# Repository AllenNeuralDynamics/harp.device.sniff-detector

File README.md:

Analog Front-End for an implanted 22KOhm thermistor.

## Features:
* 1Hz highpass filter
* 1KHz lowpass filter
* Vout = 1.65 + 100\*Vin
* Common mode thermistor input filtering
* Common mode supply voltage filtering

## Wiring Diagram
TODO

## Additional Parts
These parts aren't part of the PCBA, but they are required for a complete sensing solution:

* 22kOhm thermsistor PN: GAG22K7MCD419 [digikey link](https://www.digikey.com/en/products/detail/te-connectivity-measurement-specialties/GAG22K7MCD419/5277253)
* Flexible 2-conductor 36AWG Shielded TAU cable PN: TAU-3607.02 [link](https://www.micronmeters.com/product/tau-cable-36-awg)
* 2-Pin Molex Connector Plug PN: 0533984002 ([link](https://www.digikey.com/en/products/detail/molex/0533984002/15622916))
* 2-Pin Molex Connector Socket PN: 0151340206 ([link](https://www.digikey.com/en/products/detail/molex/0151340206/6198199))

### Old Connectors
These connectors are no longer used:
* 2-pin Mill Max Connector pins PN: 850-10-002-20-001000 [digikey link](https://www.digikey.com/en/products/detail/mill-max-manufacturing-corp/800-10-002-20-001000/7762570)
* 2-socket Mill Max Connector socket PN: 801-47-002-10-012000 [digikey link](https://www.digikey.com/en/products/detail/mill-max-manufacturing-corp/801-47-002-10-012000/7364072)

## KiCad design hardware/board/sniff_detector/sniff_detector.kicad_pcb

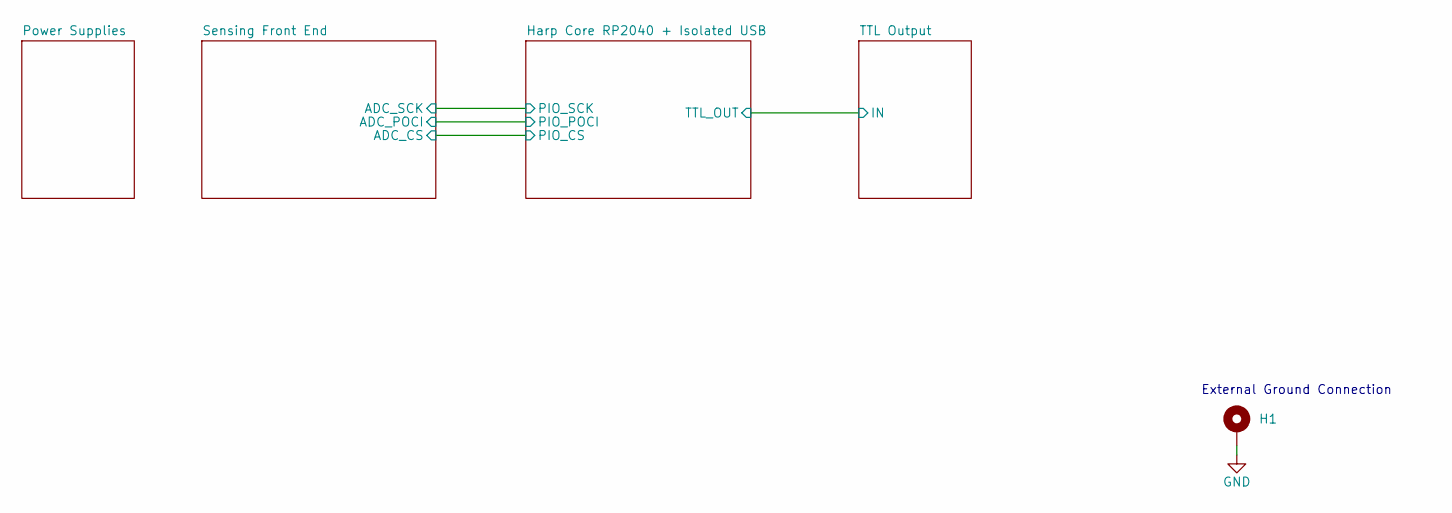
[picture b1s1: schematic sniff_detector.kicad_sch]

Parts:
H1: MountingHole_Pad; Terminal_Keystone_779x_EdgeMount_Horizontal

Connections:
GND: H1.1; also elsewhere on the board

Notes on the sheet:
External Ground Connection

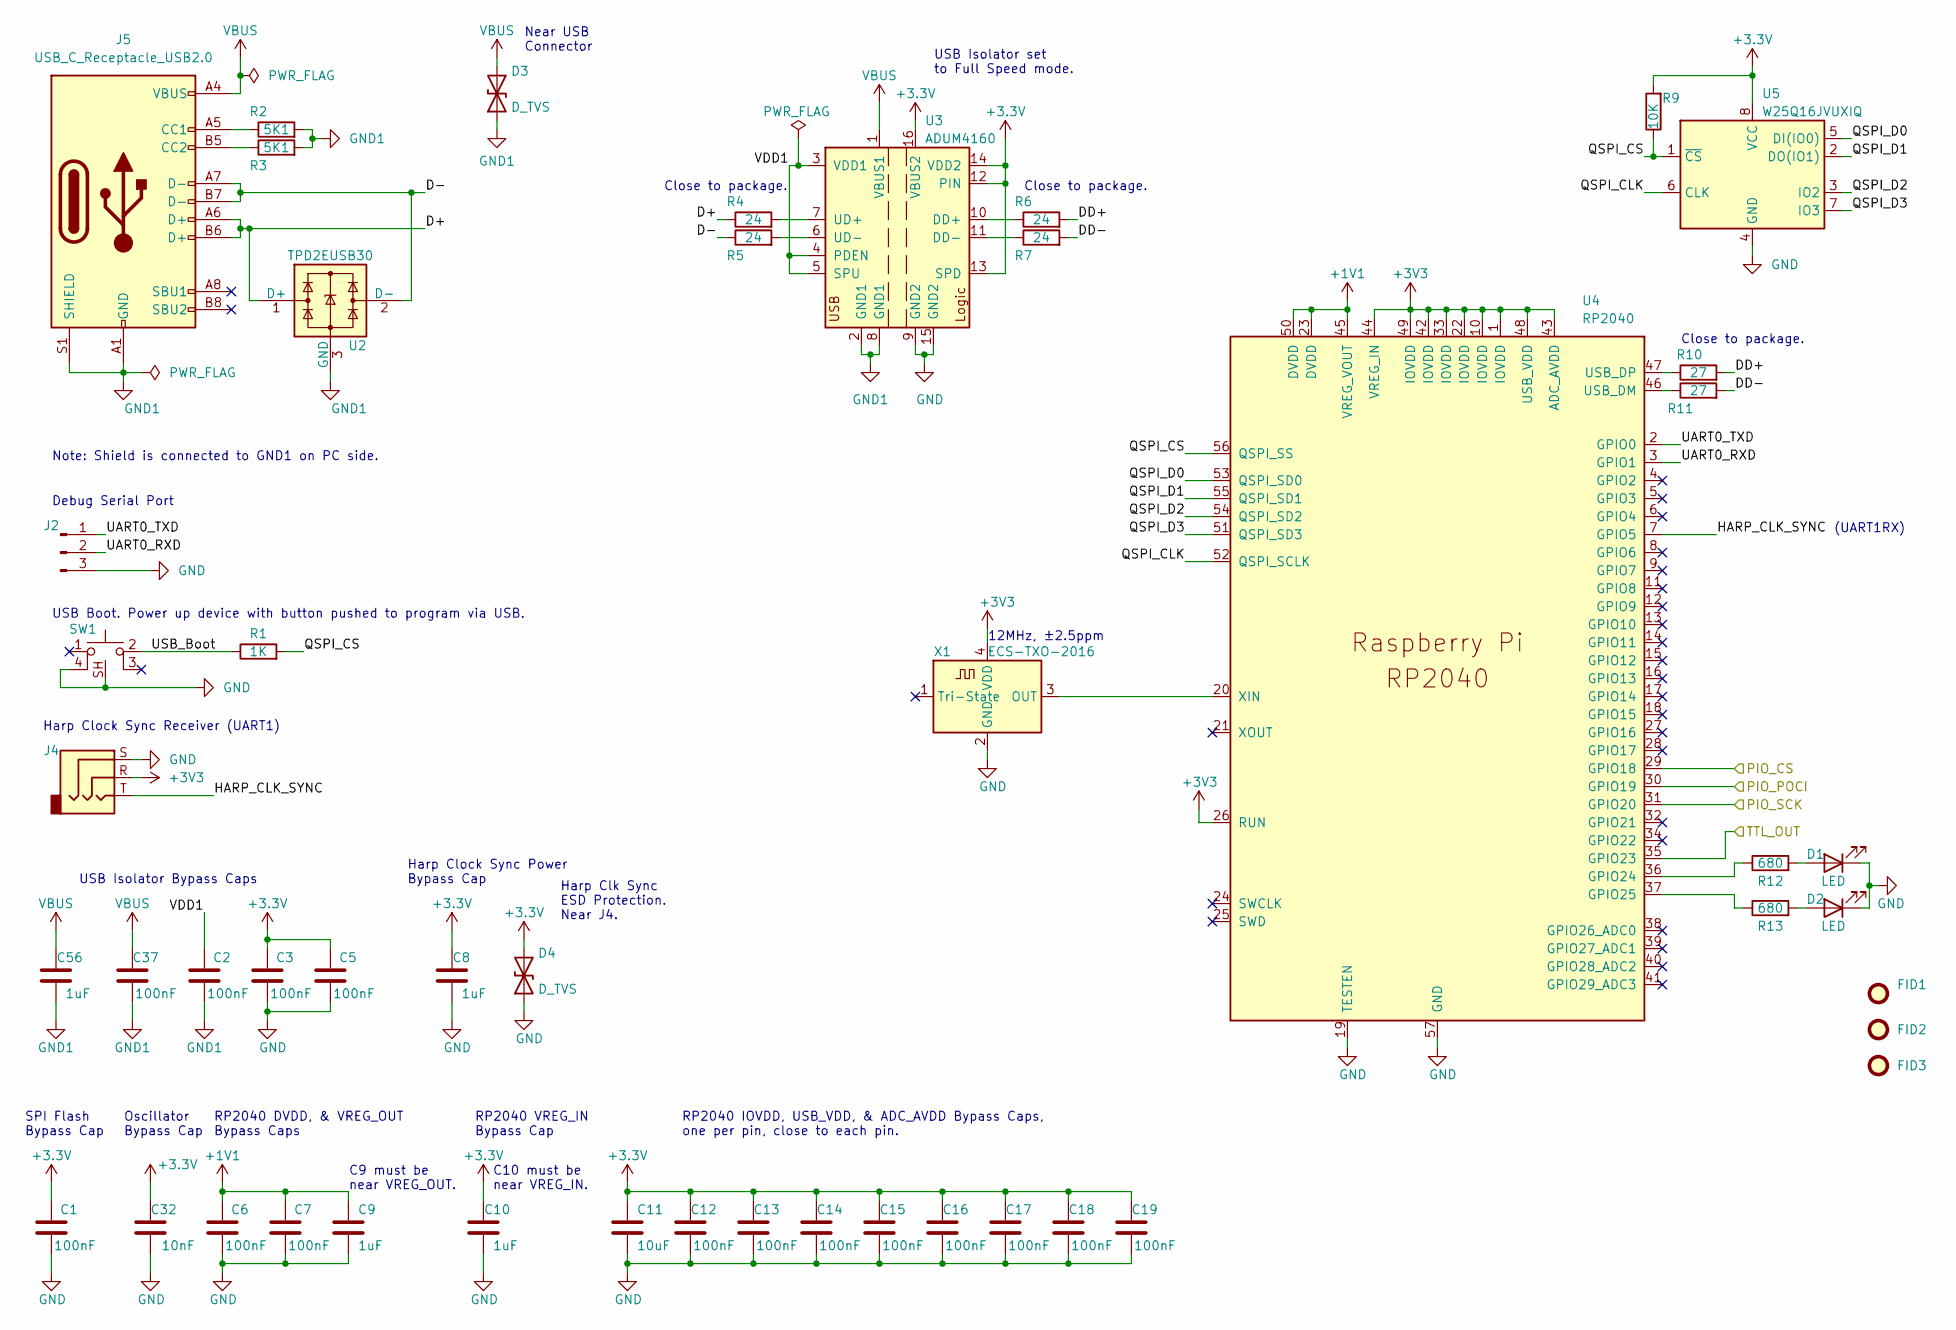
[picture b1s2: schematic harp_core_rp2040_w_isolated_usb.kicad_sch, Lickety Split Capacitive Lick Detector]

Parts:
C1, C2, C3, C5, C6, C7, C12, C13, C14, C15, C16, C17, C18, C19, C37: 100nF; C_0402_1005Metric; Rated Voltage 16V; Tolerance 10%
C8, C9, C10, C56: 1uF; C_0402_1005Metric; Rated Voltage 35V; Voltage 35V
C11: 10uF; C_0603_1608Metric; Rated Voltage 25V; Tolerance 10%
C32: 10nF; C_0402_1005Metric; Rated Voltage 25V; Tolerance 10%
D1, D2: LED; LED_0603_1608Metric_Pad1.05x0.95mm_HandSolder
D3, D4: D_TVS; D_0402_1005Metric
FID1, FID2, FID3: Fiducial; Fiducial_0.5mm_Mask1mm
J2: Conn_01x03_Male; PinHeader_1x03_P2.54mm_Vertical
J4: AudioJack3; Jack_3.5mm_CUI_SJ-3523-SMT_Horizontal
J5: USB_C_Receptacle_USB2.0; USB_C_Receptacle_JAE_DX07S016JA1R1500
R1: 1K; R_0402_1005Metric; Tolerance 1%
R2, R3: 5K1; R_0402_1005Metric; Tolerance 1%
R4, R5, R6, R7: 24; R_0402_1005Metric; Tolerance 1%
R9: 10K; R_0402_1005Metric
R10, R11: 27; R_0402_1005Metric; Tolerance 1%
R12, R13: 680; R_0402_1005Metric; Tolerance 1%
SW1: SW_Push_1P1T-SH_NO_Vertical_Wuerth_WS-TASV
U2: TPD2EUSB30; Texas_DRT-3
U3: ADUM4160; SOIC-16W_7.5x10.3mm_P1.27mm
U4: RP2040; RP2040-QFN-56
U5: W25Q16JVUXIQ; Winbond-8USON-2x3mm
X1: ECS-TXO-2016; Crystal_SMD_2016-4Pin_2.0x1.6mm; Tolerance ±2.5ppm

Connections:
+1V1: C6.2, C7.2, C9.1, U4.23 (DVDD), U4.45 (VREG_VOUT), U4.50 (DVDD)
/Harp Core RP2040 + Isolated USB/D+: J5.A6 (D+), J5.B6 (D+), R4.1, U2.1 (D+)
/Harp Core RP2040 + Isolated USB/D-: J5.A7 (D-), J5.B7 (D-), R5.1, U2.2 (D-)
/Harp Core RP2040 + Isolated USB/DD+: R6.2, R10.2
/Harp Core RP2040 + Isolated USB/DD-: R7.2, R11.2
/Harp Core RP2040 + Isolated USB/HARP_CLK_SYNC: J4.T, U4.7 (GPIO5)
/Harp Core RP2040 + Isolated USB/PIO_CS: U4.29 (GPIO18); also elsewhere on the board
/Harp Core RP2040 + Isolated USB/PIO_POCI: U4.30 (GPIO19); also elsewhere on the board
/Harp Core RP2040 + Isolated USB/PIO_SCK: U4.31 (GPIO20); also elsewhere on the board
/Harp Core RP2040 + Isolated USB/QSPI_CLK: U4.52 (QSPI_SCLK), U5.6 (CLK)
/Harp Core RP2040 + Isolated USB/QSPI_CS: R1.2, R9.1, U4.56 (QSPI_SS), U5.1 (~CS)
/Harp Core RP2040 + Isolated USB/QSPI_D0: U4.53 (QSPI_SD0), U5.5 (DI(IO0))
/Harp Core RP2040 + Isolated USB/QSPI_D1: U4.55 (QSPI_SD1), U5.2 (DO(IO1))
/Harp Core RP2040 + Isolated USB/QSPI_D2: U4.54 (QSPI_SD2), U5.3 (IO2)
/Harp Core RP2040 + Isolated USB/QSPI_D3: U4.51 (QSPI_SD3), U5.7 (IO3)
/Harp Core RP2040 + Isolated USB/TTL_OUT: U4.35 (GPIO23); also elsewhere on the board
/Harp Core RP2040 + Isolated USB/UART0_RXD: J2.2, U4.3 (GPIO1)
/Harp Core RP2040 + Isolated USB/UART0_TXD: J2.1, U4.2 (GPIO0)
/Harp Core RP2040 + Isolated USB/USB_Boot: R1.1, SW1.2
/Harp Core RP2040 + Isolated USB/VDD1: C2.2, U3.3 (VDD1), U3.4 (PDEN), U3.5 (SPU)
GND: C1.1, C3.1, C5.1, C6.1, C7.1, C8.2, C9.2, C10.2, C11.2, C12.1, C13.1, C14.1, C15.1, C16.1, C17.1, C18.1, C19.1, C32.1, D1.1 (K), D2.1 (K), D4.1 (A1), J2.3, J4.S, SW1.4, SW1.SH, U3.9 (GND2), U3.15 (GND2), U4.19 (TESTEN), U4.57 (GND), U5.4 (GND), X1.2 (GND); also elsewhere on the board
GND1: C2.1, C37.1, C56.2, D3.1 (A1), J5.A1 (GND), J5.A12 (GND), J5.B1 (GND), J5.B12 (GND), J5.S1 (SHIELD), R2.2, R3.2, U2.3 (GND), U3.2 (GND1), U3.8 (GND1)
unnamed: D1.2 (A), R12.2
unnamed: D2.2 (A), R13.2
unnamed: J5.A5 (CC1), R2.1
unnamed: J5.B5 (CC2), R3.1
unnamed: R6.1, U3.10 (DD+)
unnamed: R7.1, U3.11 (DD-)
unnamed: R4.2, U3.7 (UD+)
unnamed: R5.2, U3.6 (UD-)
unnamed: R12.1, U4.36 (GPIO24)
unnamed: R13.1, U4.37 (GPIO25)
unnamed: R11.1, U4.46 (USB_DM)
unnamed: R10.1, U4.47 (USB_DP)
unnamed: U4.20 (XIN), X1.3 (OUT)
VBUS: C37.2, C56.1, D3.2 (A2), J5.A4 (VBUS), J5.A9 (VBUS), J5.B4 (VBUS), J5.B9 (VBUS), U3.1 (VBUS1)

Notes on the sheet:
Close to package.
Near USB Connector
(UART1RX)
Harp Clk Sync ESD Protection. Near J4.
RP2040 VREG_IN Bypass Cap
Oscillator Bypass Cap
Harp Clock Sync Power Bypass Cap
C10 must be near VREG_IN.
RP2040 DVDD, & VREG_OUT Bypass Caps
Debug Serial Port
USB Boot. Power up device with button pushed to program via USB.
C9 must be near VREG_OUT.
Harp Clock Sync Receiver (UART1)
12MHz, ±2.5ppm
Note: Shield is connected to GND1 on PC side.
RP2040 IOVDD, USB_VDD, & ADC_AVDD Bypass Caps, one per pin, close to each pin.
USB Isolator Bypass Caps
SPI Flash Bypass Cap
USB Isolator set to Full Speed mode.

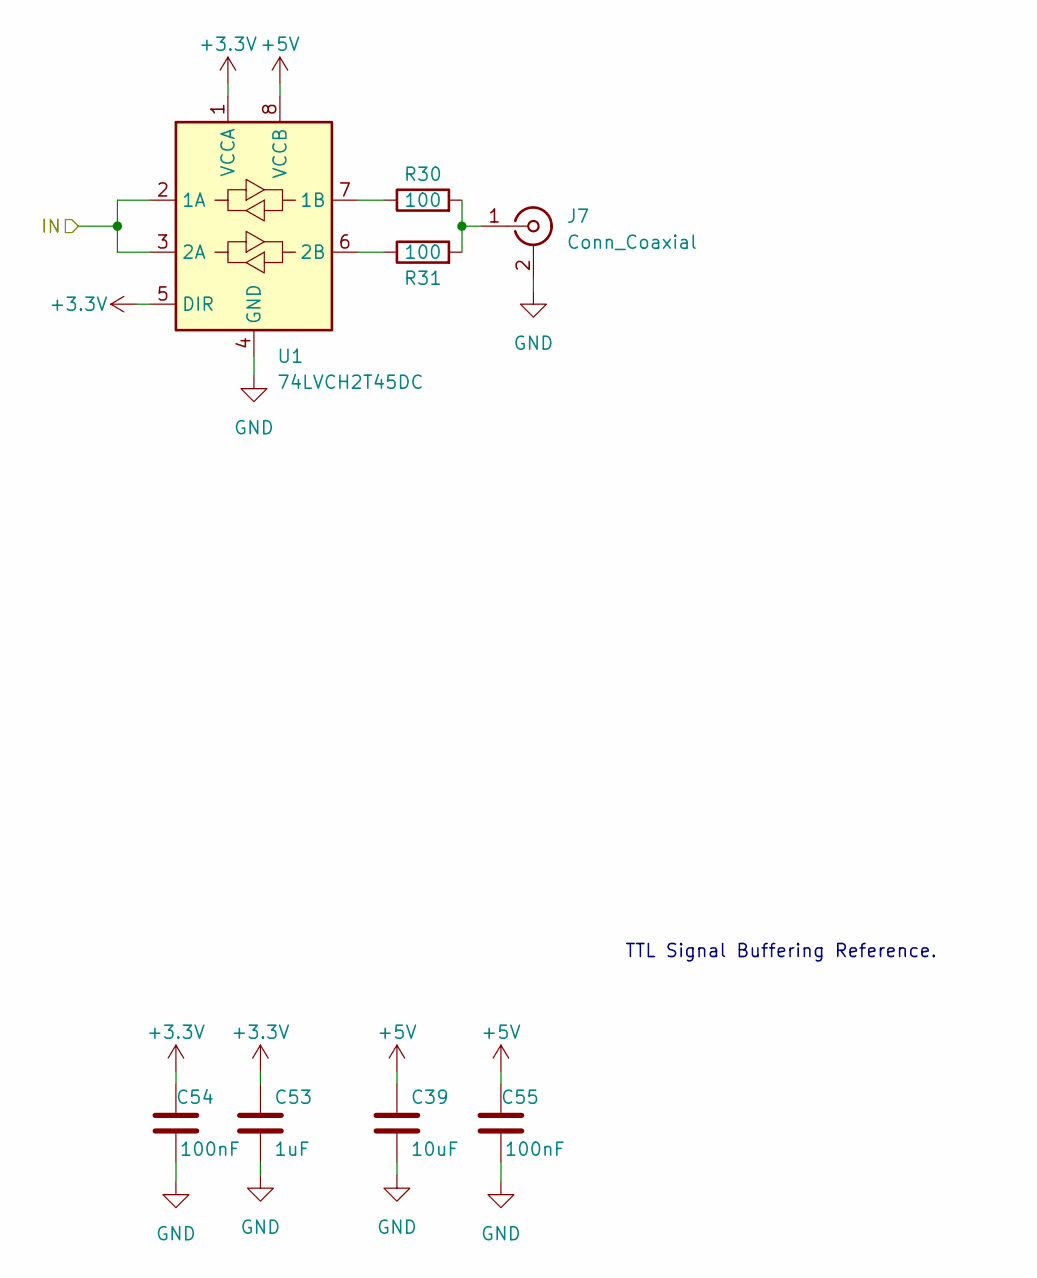
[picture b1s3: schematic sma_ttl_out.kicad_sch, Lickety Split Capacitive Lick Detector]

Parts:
C39: 10uF; C_0603_1608Metric; Rated Voltage 25V; Tolerance 10%
C53: 1uF; C_0402_1005Metric; Rated Voltage 35V; Voltage 35V
C54, C55: 100nF; C_0402_1005Metric; Rated Voltage 16V; Tolerance 10%
J7: Conn_Coaxial; SMA_TE_Connectivity_CONSMA002-SMD-G-T_Horizontal
R30, R31: 100; R_0603_1608Metric_Pad0.98x0.95mm_HandSolder; Tolerance 1%
U1: 74LVCH2T45DC; VSSOP-8_2.3x2mm_P0.5mm

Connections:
+5V: C39.1, C55.2, U1.8 (VCCB); also elsewhere on the board
/Harp Core RP2040 + Isolated USB/TTL_OUT: U1.2 (1A), U1.3 (2A); also elsewhere on the board
GND: C39.2, C53.2, C54.1, C55.1, J7.2 (Ext), U1.4 (GND); also elsewhere on the board
unnamed: J7.1 (In), R30.2, R31.2
unnamed: R30.1, U1.7 (1B)
unnamed: R31.1, U1.6 (2B)

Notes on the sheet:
TTL Signal Buffering Reference.

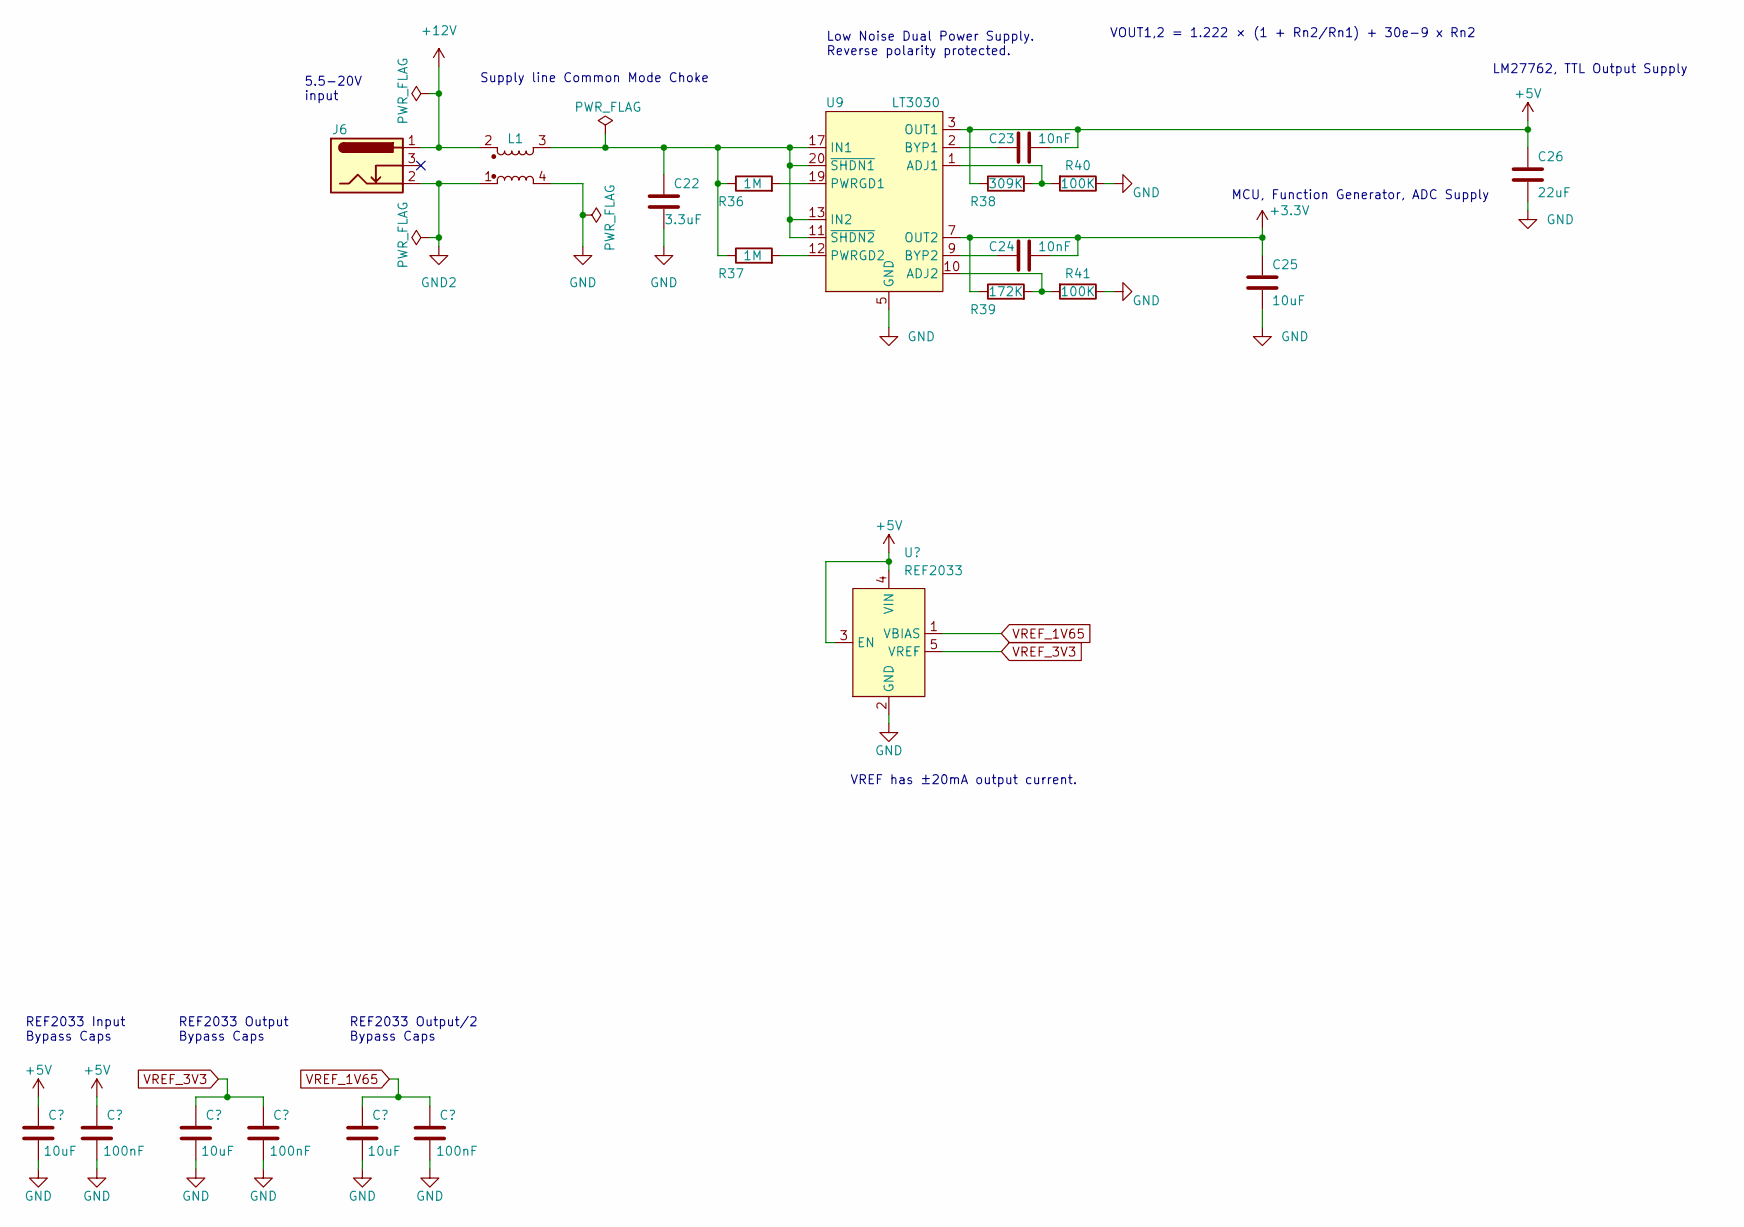
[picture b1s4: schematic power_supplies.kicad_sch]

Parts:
C22: 3.3uF; C_0805_2012Metric; Rated Voltage 25V; Tolerance 10%
C23, C24: 10nF; C_0402_1005Metric; Rated Voltage 25V; Tolerance 10%
C25: 10uF; C_0603_1608Metric; Rated Voltage 25V; Tolerance 10%
C26: 22uF; C_0805_2012Metric; Rated Voltage 25V; Voltage 25V
C35, C38, C41: 10uF; C_0603_1608Metric; Tolerance 10%; Voltage 25V
C36, C40, C42: 100nF; C_0402_1005Metric; Tolerance 10%; Voltage 16V
J6: Barrel_Jack_Switch; BarrelJack_CUI_PJ-102AH_Horizontal
L1: L_Coupled_1423; L_CommonModeChoke_TDKCorporation_1210
R36, R37: 1M; R_0402_1005Metric; Tolerance 1%
R38: 309K; R_0402_1005Metric; Tolerance 0.1%
R39: 172K; R_0402_1005Metric; Tolerance 1%
R40, R41: 100K; R_0402_1005Metric; Tolerance 0.1%
U8: REF2033; SOT-23-5
U9: LT3030; ETSSOP-20-1EP_4.4x6.5mm_P0.65mm_EP3x4.2mm

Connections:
+5V: C23.1, C26.1, C35.1, C36.2, R38.1, U8.3 (EN), U8.4 (VIN), U9.3 (OUT1), U9.4 (OUT1); also elsewhere on the board
+12V: J6.1, L1.2
GND: C22.2, C25.2, C26.2, C35.2, C36.1, C38.2, C40.1, C41.2, C42.1, L1.4, R40.1, R41.1, U8.2 (GND), U9.5 (GND), U9.6 (GND), U9.15 (GND), U9.16 (GND), U9.21 (GND); also elsewhere on the board
GND2: J6.2, L1.1
IN1: C22.1, L1.3, R36.1, R37.1, U9.11 (~SHDN2), U9.13 (IN2), U9.14 (IN2), U9.17 (IN1), U9.18 (IN1), U9.20 (~SHDN1)
unnamed: R38.2, R40.2, U9.1 (ADJ1)
unnamed: R39.2, R41.2, U9.10 (ADJ2)
unnamed: C23.2, U9.2 (BYP1)
unnamed: C24.2, U9.9 (BYP2)
unnamed: R36.2, U9.19 (PWRGD1)
unnamed: R37.2, U9.12 (PWRGD2)
VREF_1V65: C41.1, C42.2, U8.1 (VBIAS); also elsewhere on the board
VREF_3V3: C38.1, C40.2, U8.5 (VREF); also elsewhere on the board

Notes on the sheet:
REF2033 Input Bypass Caps
REF2033 Output/2 Bypass Caps
MCU, Function Generator, ADC Supply
5.5-20V input
REF2033 Output Bypass Caps
VOUT1,2 = 1.222 × (1 + Rn2/Rn1) + 30e-9 x Rn2
Supply line Common Mode Choke
VREF has ±20mA output current.
Low Noise Dual Power Supply. Reverse polarity protected.
LM27762, TTL Output Supply

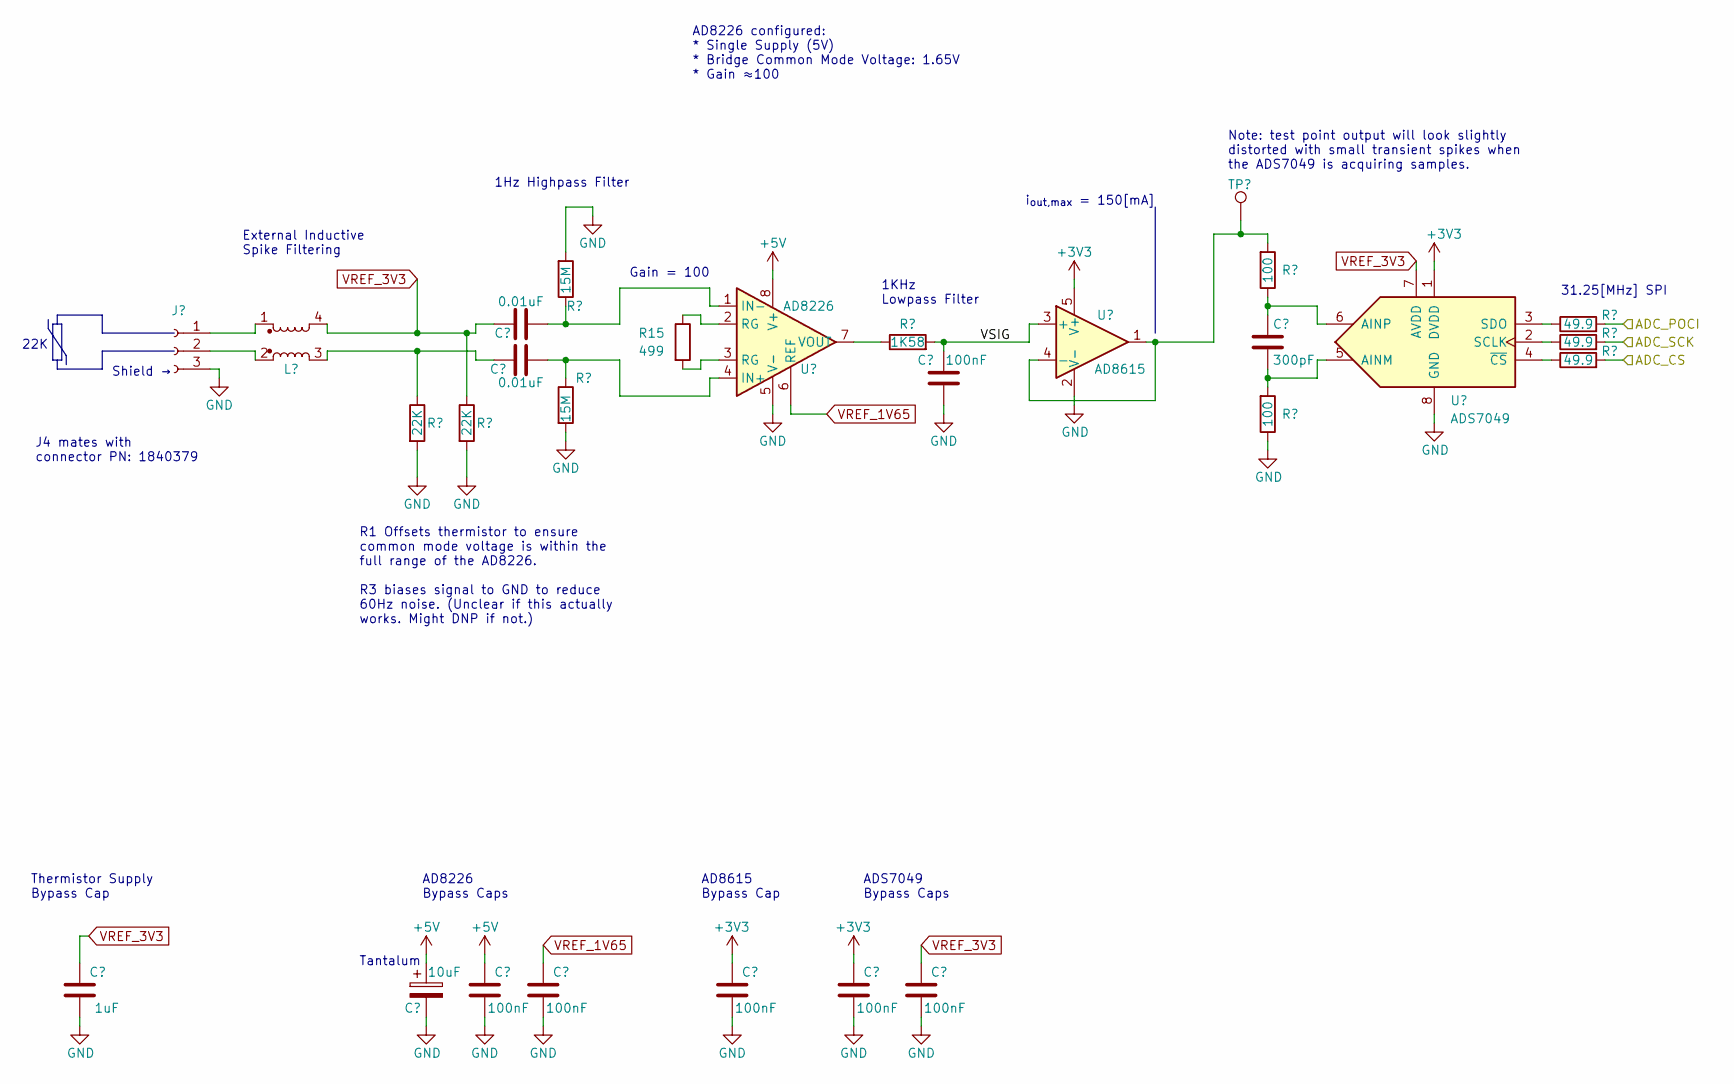
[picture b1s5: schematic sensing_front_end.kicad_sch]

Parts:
C4: 1uF; C_0402_1005Metric; Voltage 35V; Rated Voltage 35V
C20: 10uF; C_0805_2012Metric; Rated Voltage 10V; Tolerance 20%
C21, C29, C30, C31, C33: 100nF; C_0402_1005Metric; Rated Voltage 16V; Tolerance 10%
C27, C28: 0.01uF; C_1206_3216Metric; Tolerance 1%
C34: 100nF; C_0402_1005Metric; Tolerance 10%; Voltage 16V
C52: 300pF; C_0402_1005Metric; Tolerance 1%
J1: Conn_01x03_Female; PhoenixContact_MC_1,5_3-G-3.5_1x03_P3.50mm_Horizontal
L2: L_Coupled_1423; L_CommonModeChoke_TDKCorporation_1210
R8, R18: 22K; R_0603_1608Metric; Tolerance 0.1%
R14, R17: 15M; R_1206_3216Metric; Tolerance 1%
R15: 499; R_0603_1608Metric_Pad0.98x0.95mm_HandSolder; Tolerance 0.1%
R16: 1K58; R_0603_1608Metric; Tolerance 0.1%
R28, R29, R44: 49.9; R_0402_1005Metric
R42, R43: 100; R_0402_1005Metric; Tolerance 0.1%
TP1: TestPoint; TestPoint_Keystone_5027_Miniature
U6: AD8615; TSOT-23-5
U7: AD8226; MSOP-8_3x3mm_P0.65mm
U13: ADS7049; VSSOP-8_2.3x2mm_P0.5mm

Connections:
+5V: C20.1, C21.2, U7.8 (V+); also elsewhere on the board
/Harp Core RP2040 + Isolated USB/PIO_CS: R44.2; also elsewhere on the board
/Harp Core RP2040 + Isolated USB/PIO_POCI: R28.2; also elsewhere on the board
/Harp Core RP2040 + Isolated USB/PIO_SCK: R29.2; also elsewhere on the board
/Sensing Front End/VSIG: C34.1, R16.2, U6.3 (+)
GND: C4.1, C20.2, C21.1, C29.1, C30.1, C31.1, C33.1, C34.2, J1.3, R8.2, R14.2, R17.2, R18.2, R42.1, U6.2 (V-), U7.5 (V-), U13.8 (GND); also elsewhere on the board
unnamed: C28.1, L2.3, R8.1
unnamed: J1.1, L2.1
unnamed: J1.2, L2.2
unnamed: R15.1, U7.2 (RG)
unnamed: R15.2, U7.3 (RG)
unnamed: R43.2, TP1.1, U6.1, U6.4 (-)
unnamed: C28.2, R14.1, U7.4 (IN+)
unnamed: C27.2, R17.1, U7.1 (IN-)
unnamed: R16.1, U7.7 (VOUT)
unnamed: C52.2, R42.2, U13.5 (AINM)
unnamed: C52.1, R43.1, U13.6 (AINP)
unnamed: R29.1, U13.2 (SCLK)
unnamed: R28.1, U13.3 (SDO)
unnamed: R44.1, U13.4 (~CS)
VREF_1V65: C29.2, U7.6 (REF); also elsewhere on the board
VREF_3V3: C4.2, C27.1, C33.2, L2.4, R18.1, U13.7 (AVDD); also elsewhere on the board

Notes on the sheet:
J4 mates with connector PN: 1840379
Thermistor Supply Bypass Cap
Shield →
Tantalum
Note: test point output will look slightly distorted with small transient spikes when the ADS7049 is acquiring samples.
i_{out,max} = 150[mA]
ADS7049 Bypass Caps
R1 Offsets thermistor to ensure common mode voltage is within the full range of the AD8226. R3 biases signal to GND to reduce 60Hz noise. (Unclear if this actually works. Might DNP if not.)
1Hz Highpass Filter
AD8615 Bypass Cap
AD8226 configured: * Single Supply (5V) * Bridge Common Mode Voltage: 1.65V * Gain ≈100
31.25[MHz] SPI
External Inductive Spike Filtering
22K
AD8226 Bypass Caps
1KHz Lowpass Filter
Gain = 100

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
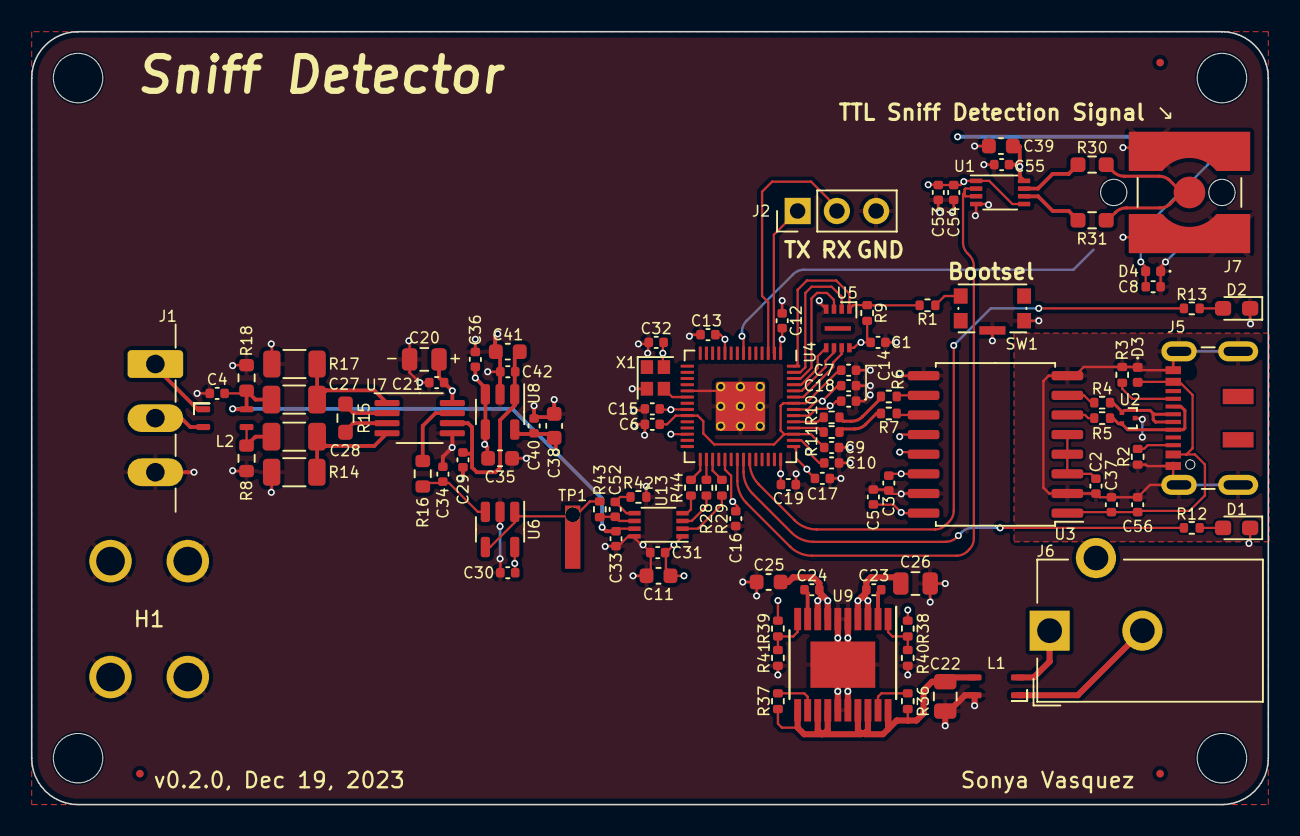
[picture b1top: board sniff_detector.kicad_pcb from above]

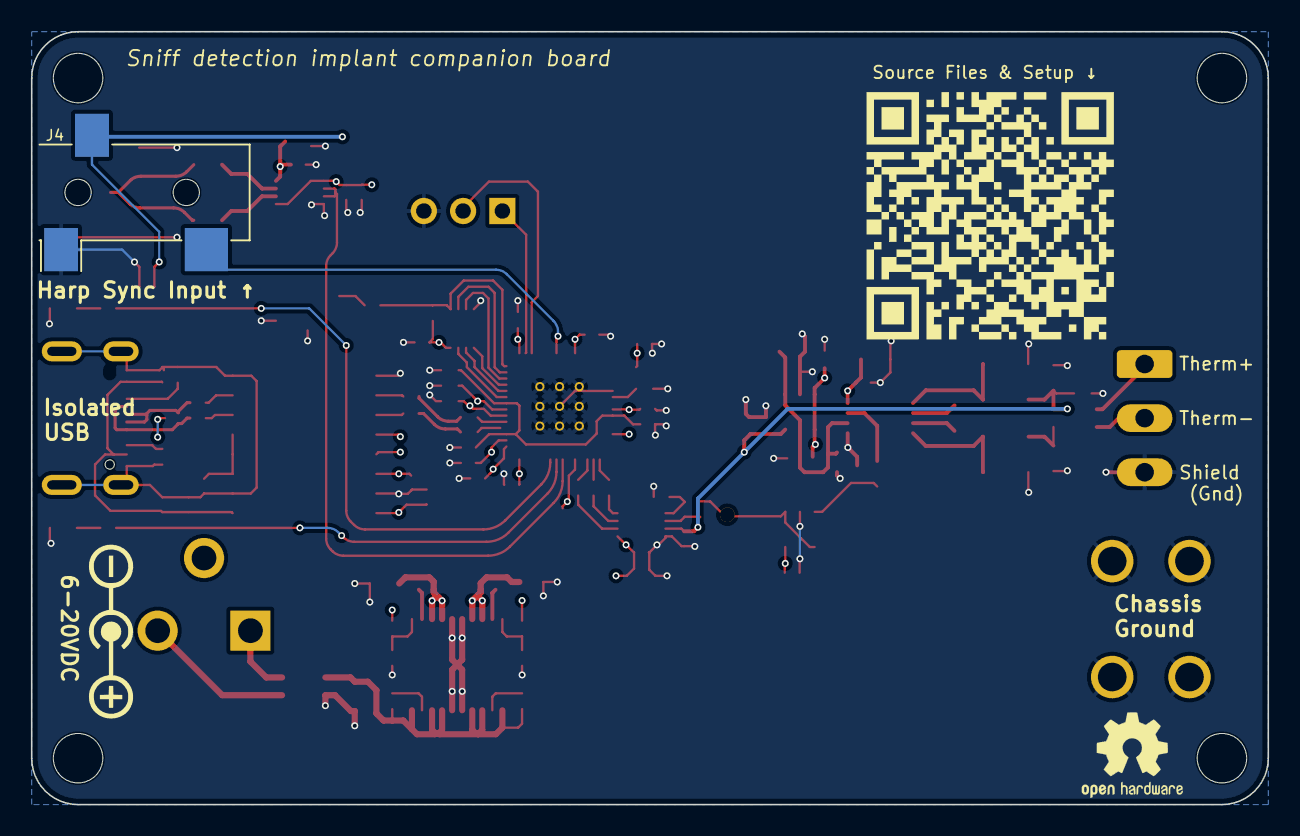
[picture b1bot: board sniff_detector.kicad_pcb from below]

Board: 4 copper layers, 80.0 x 50.0 mm, 109 parts (3 on the bottom side), 67 nets.

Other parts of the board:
G3: LOGO
REF1: OSHW-Logo2_7.3x6mm_SilkScreen

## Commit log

2023-07-31 annotate schematic
2023-08-03 annotate rev1
2023-08-03 update references
2023-12-19 complete pcb v0.2
2023-12-19 update gitignore
2023-12-20 draft firmware
2023-12-20 update dispatch frequency
2024-01-11 add board step file to repo
2024-01-11 add enclosure
2024-01-26 update lick detector registers
2024-01-26 add sensor error state bitfield interpretation
2024-02-06 get mvp working
2024-02-06 add pyharp test scripts
2024-02-27 Add interface draft
2024-03-05 draft register functionality
2024-03-06 Fix metadata reference
2024-03-06 Update schema and interface
2024-03-06 update default sensor dispatch rate
2024-04-12 bugfix dma race condition
2024-07-24 append git hash to executable name
2024-08-23 upate lick detector enclosure
2024-11-08 Update bonsai generators
2024-11-10 Favor harp-tech as source of device schema
2025-02-06 update harp core
2025-02-06 add git hash and populate usb descriptors
2025-02-07 remove hash from binary name
2025-02-21 update pyharp examples
2025-03-20 Update README.md
    add new connector part numbers
